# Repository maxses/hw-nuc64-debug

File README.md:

# NUC64DEBUG

## Overview

|           |                                                               |
|:----------|:--------------------------------------------------------------|
| Name      | NUC64DEBUG                                                    |
| HW-Rev    | v0.3.x                                                        |
| Docu      | 20260117                                                      |
| Dimensions| 17.30mm x 30.43mm                                             |

Small adapter PCB to connect a STM32 based custom PCB via 10P-FPC with the STLink-part
of an Nucleo64-Board.

## PCB

| Top                                           |  Bottom                                              |
|:----------------------------------------------|:-----------------------------------------------------|
|  |  |

<div class="pagebreak"> </div>

## Connectors

### DBG1

| Connector-pin |  Function              |
|:--------------|:-----------------------|
| 1             | VDD Target             |
| 2             | SWCLK                  |
| 3             | GND                    |
| 4             | SWDIO                  |
| 5             | NRST                   |
| 6             | NC (Reserved for SWO)  |
| 7             | UART TX (Target)       |
| 8             | UART RX (Target)       |
| 9             | VIN 5V                 |
| 10            | BOOT0                  |

## J1

| Connector-pin |  Function              |
|:--------------|:-----------------------|
| 1             | VDD                    |
| 2             | SWCLK                  |
| 3             | GND                    |
| 4             | SWDIO                  |
| 5             | NRST                   |
| 6             | SWO                    |

## UART1

| Connector-pin |  Function                                      |
|:--------------|:-----------------------------------------------|
| 1             | TX (ST-Link / Host) -> yellow on adapter cable |
| 2             | RX (ST-Link / Host) -> red on adapter cable    |

## Errata

* If you have problems with the  UART you may need to update firmware of STLink.
Version V2J20M4 did not work, after update to V2J38M27 problems disappeared.

* V0.2.x: Boot-Button not functional. Connect J2-Pin2(VDD) to button pad in the corner.

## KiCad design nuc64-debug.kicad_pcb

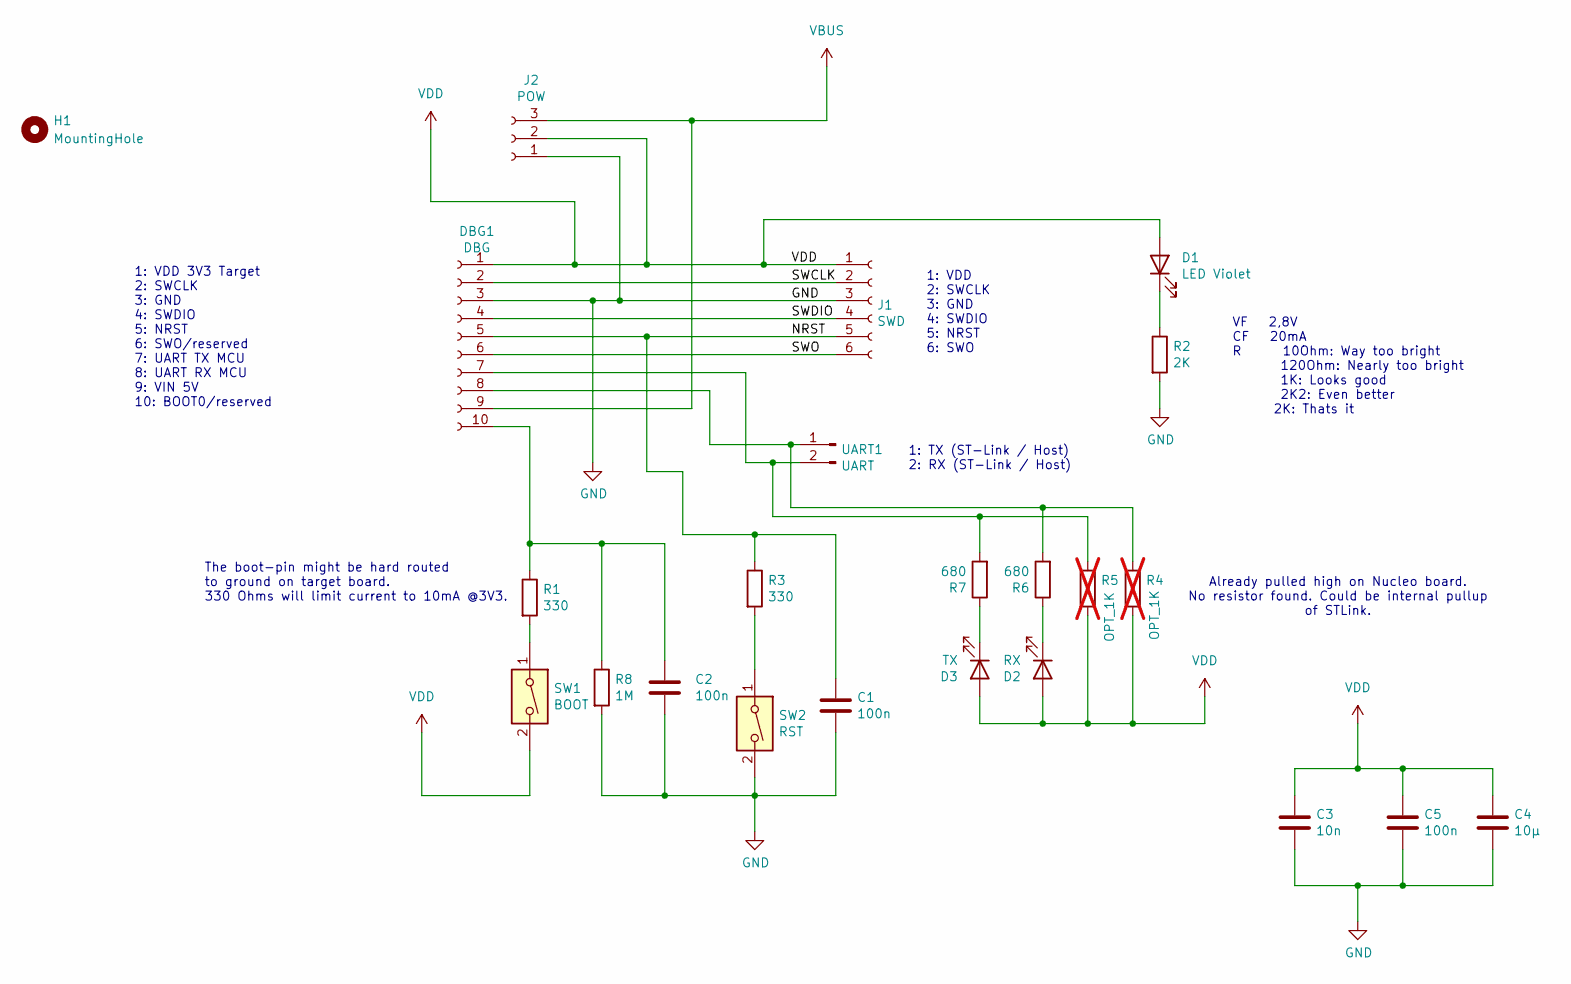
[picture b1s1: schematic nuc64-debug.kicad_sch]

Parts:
C1, C2, C5: 100n; C_0603_1608Metric
C3: 10n; C_0603_1608Metric
C4: 10µ; C_0603_1608Metric
D1: LED Violet; LED_0603_1608Metric
D2: RX; LED_0603_1608Metric
D3: TX; LED_0603_1608Metric
DBG1: DBG; Hirose_FH12-10S-0.5SH_1x10-1MP_P0.50mm_Horizontal
H1: MountingHole; MountingHole_2.2mm_M2_DIN965
J1: SWD; PinSocket_1x06_P2.54mm_Vertical
J2: POW; PinHeader_1x03_P2.54mm_Vertical
R1, R3: 330; R_0603_1608Metric
R2: 2K; R_0603_1608Metric
R4, R5: OPT_1K; R_0603_1608Metric; not fitted
R6, R7: 680; R_0603_1608Metric
R8: 1M; R_0603_1608Metric
SW1: BOOT; SW_SPST_Omron_B3FS-105xP
SW2: RST; SW_SPST_Omron_B3FS-105xP
UART1: UART; PinSocket_1x02_P2.54mm_Vertical

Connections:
/NRST: C1.1, DBG1.5, J1.5, R3.1
/SWCLK: DBG1.2, J1.2
/SWDIO: DBG1.4, J1.4
/SWO: DBG1.6, J1.6
GND: C1.2, C2.2, C3.2, C4.2, C5.2, DBG1.3, J1.3, J2.1, R2.2, R8.2, SW2.2
unnamed: D1.1 (K), R2.1
unnamed: D2.1 (K), R6.1
unnamed: D3.1 (K), R7.1
unnamed: DBG1.7, R5.1, R7.2, UART1.2
unnamed: DBG1.8, R4.1, R6.2, UART1.1
unnamed: C2.1, DBG1.10, R1.1, R8.1
unnamed: R1.2, SW1.1
unnamed: R3.2, SW2.1
VBUS: DBG1.9, J2.3
VDD: C3.1, C4.1, C5.1, D1.2 (A), D2.2 (A), D3.2 (A), DBG1.1, J1.1, J2.2, R4.2, R5.2, SW1.2

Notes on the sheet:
1: TX (ST-Link / Host) 2: RX (ST-Link / Host)
VF 2,8V CF 20mA R 10Ohm: Way too bright 120Ohm: Nearly too bright 1K: Looks good 2K2: Even better 2K: Thats it
The boot-pin might be hard routed to ground on target board. 330 Ohms will limit current to 10mA @3V3.
1: VDD 3V3 Target 2: SWCLK 3: GND 4: SWDIO 5: NRST 6: SWO/reserved 7: UART TX MCU 8: UART RX MCU 9: VIN 5V 10: BOOT0/reserved
1: VDD 2: SWCLK 3: GND 4: SWDIO 5: NRST 6: SWO
Already pulled high on Nucleo board. No resistor found. Could be internal pullup of STLink.

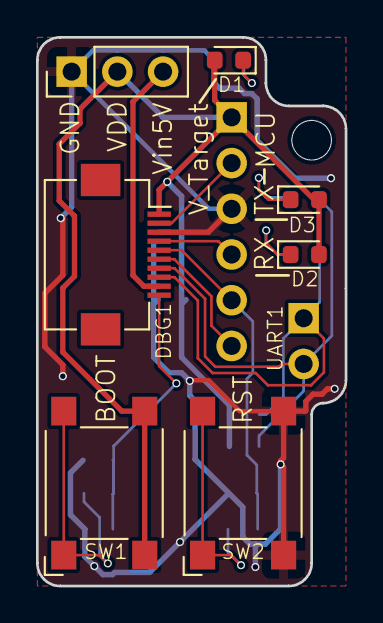
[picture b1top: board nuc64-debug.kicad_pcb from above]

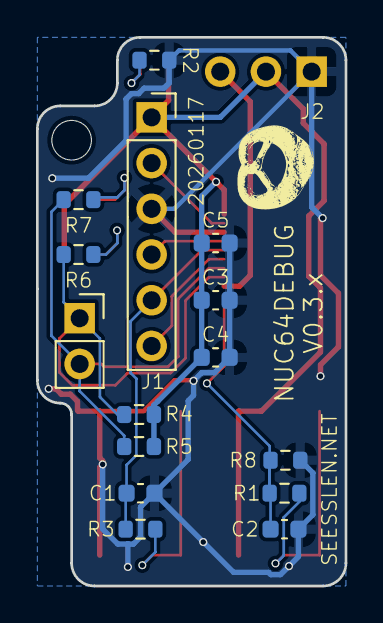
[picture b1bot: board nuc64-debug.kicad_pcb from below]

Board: 2 copper layers, 17.1 x 30.5 mm, 23 parts (15 on the bottom side), 15 nets.

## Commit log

2018-10-06 initial import
2018-10-06 added git ignore file
2018-10-06 added some grounding vias
2018-10-16 fixed drawings
2021-02-13 added erata.txt
2021-07-14 First draft for 0.2.x
    Uart TX/RX have been swapped
    Buttons for Reset/Boot0 have been added
    Pinheader for power pins has been added
2021-07-14 shrink
2021-07-14 make the design category 'easy' for aisler design rules
2021-07-14 polish
2021-10-05 added/updated documentation
2026-01-17 [#32/#388] Boot0-button pulls high; updated symbols
2026-01-17 Finished routing
2026-01-17 Fixed trace width
2026-01-17 Added UART LEDs
2026-01-17 Added mounting hole for soldering
2026-01-17 Added Brezel
2026-01-17 Updated BOM
2026-01-17 Made UART pullups optional
2026-02-02 Updated values for R6/R7
2026-02-02 Added images
2026-02-02 Updated git ignore file
2026-02-02 Fixed docu
2026-02-02 draft1
2026-02-02 Removed CSS parts from readme
